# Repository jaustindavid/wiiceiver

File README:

http://austindavid.com/t/wiiceiver-github

The Wiiceiver is a drop-in "plug and play" replacement for a
standard R/C receiver.  It has a Nintendo Wii Nunchuck 
connection, a 3-pin ESC connector, and an available connector
for an external BEC if required.  

The Wiiceiver is intended for use on an electric skateboard.
The Y-axis (up/down) is throttle -- push up to speed up,
middle is neutral, down is brakes.  These function roughly
the same as on a standard RC transmitter.

Wiiceiver also implements a few additional functions:
- X/Y joystick axes, X/Y/Z accelerometers, and the two buttons 
  are monitored to confirm that the nunchuck is "active" -- 
  as opposed to dropped or low battery.  When "inactive" the
  wiiceiver returns to neutral, and will not re-start until 
  it detects and active neutral signal
- C button is "cruise control" -- press and hold C to maintain
  the current throttle level.  Drop the joystick to neutral to
  cruise.  While holding C, pressing the joystick "up" will
  increase speed gently, "down" will decrease speed.  
  Releasing C returns to neutral.
- Control smoothing: Wiiceiver implemenets an exponential 
  algorithm to smooth the controller input.  As currently
  tuned, an instant 0-100% throttle input will result in a
  gradual change to the ESC over the course of about 1s.
- 2.0 uses a "floating ceiling" for predictable acceleration
  damping and more responsive throttle.

It has been tested to work with a corded Nintendo nunchuck, a 
Memorex wireless nunchuck, and a Nyko Kama wireless nunchuck.

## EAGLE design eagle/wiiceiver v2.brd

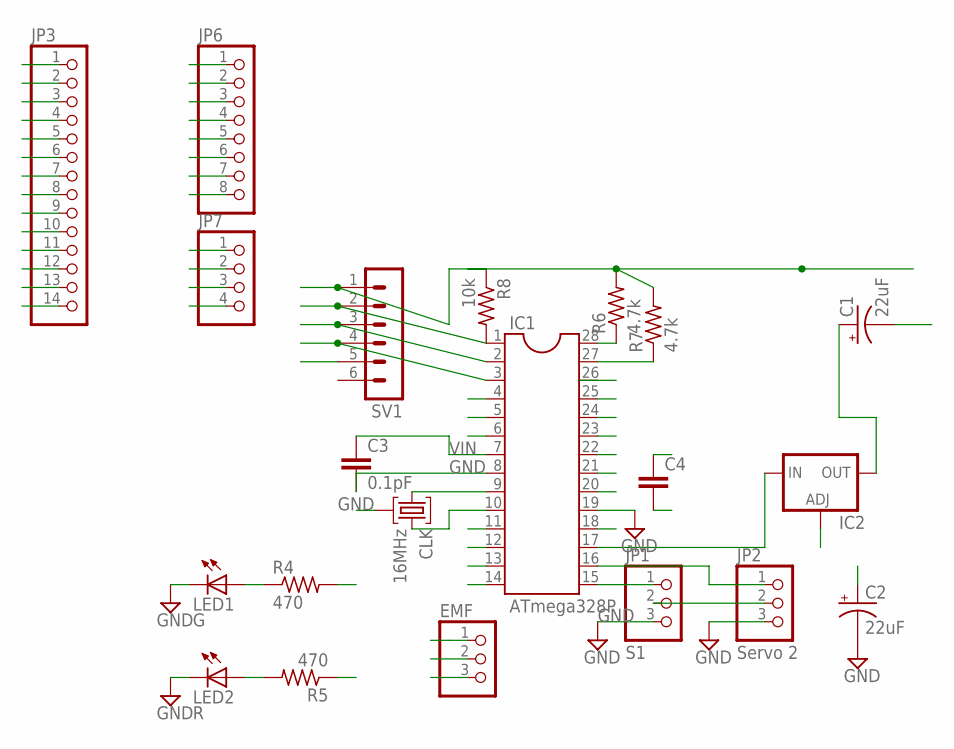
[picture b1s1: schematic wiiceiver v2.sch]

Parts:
C1, C2: 22uF; B45181A
C3: 0.1pF; C5B2.5
C4: C5/2.5; C5B2.5
CLK: 16MHz; HC49U
EMF: PINHD-1X3; 1X03
IC1: ATmega328P; DIL28-3
IC2: LM317TS; 317TS
JP1: S1; 1X03
JP2: Servo 2; 1X03
JP3: PINHD-1X14; 1X14
JP6: PINHD-1X8; 1X08
JP7: PINHD-1X4; 1X04
LED1: G; LED3MM
LED2: R; LED3MM
R4, R5: 470; 0204V
R6, R7: 4.7k; 0204V
R8: 10k; 0204V
SV1: MA06-1

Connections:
A0: IC1.23, JP3.6
A1: IC1.24, JP3.5
A2: IC1.25, JP3.4
A3: IC1.26, JP3.3
A4: IC1.27, JP3.2, R7.1
A5: IC1.28, JP3.1, R6.1
D0: IC1.2, JP6.2, SV1.3
D1: IC1.3, JP6.3, SV1.4
D2: IC1.4, JP6.4
D3: IC1.5, JP6.5
D4: IC1.6, JP6.6
D5: IC1.11, JP7.1
D6: IC1.12, JP7.2, R4.2
D7: IC1.13, JP7.3
D8: IC1.14, JP7.4, R5.1
D9: IC1.15, JP1.1, JP3.14
D10: IC1.16, JP2.1, JP3.13
D11: IC1.17, IC2.3 (IN), JP3.12
D12: IC1.18, JP3.11
D13: JP3.10
GND: C1.-, C2.-, C3.2, C4.2, CLK.2, EMF.2, IC1.8, IC1.19, IC1.22, IC2.1 (ADJ), JP1.3, JP2.3, JP3.7, JP6.8, LED1.K (C), LED2.K (C), SV1.5
unnamed: LED2.A, R5.2
unnamed: LED1.A, R4.1
unnamed: CLK.3, IC1.10
unnamed: CLK.1, IC1.9
unnamed: C1.+, IC2.2 (OUT)
RST: IC1.1, JP6.1, R8.2, SV1.2
VIN: C3.1, C4.1, EMF.3, IC1.7, IC1.20, IC1.21, JP3.8, JP3.9, JP6.7, R6.2, R7.2, R8.1, SV1.1
VRAW: C2.+, EMF.1, JP1.2, JP2.2

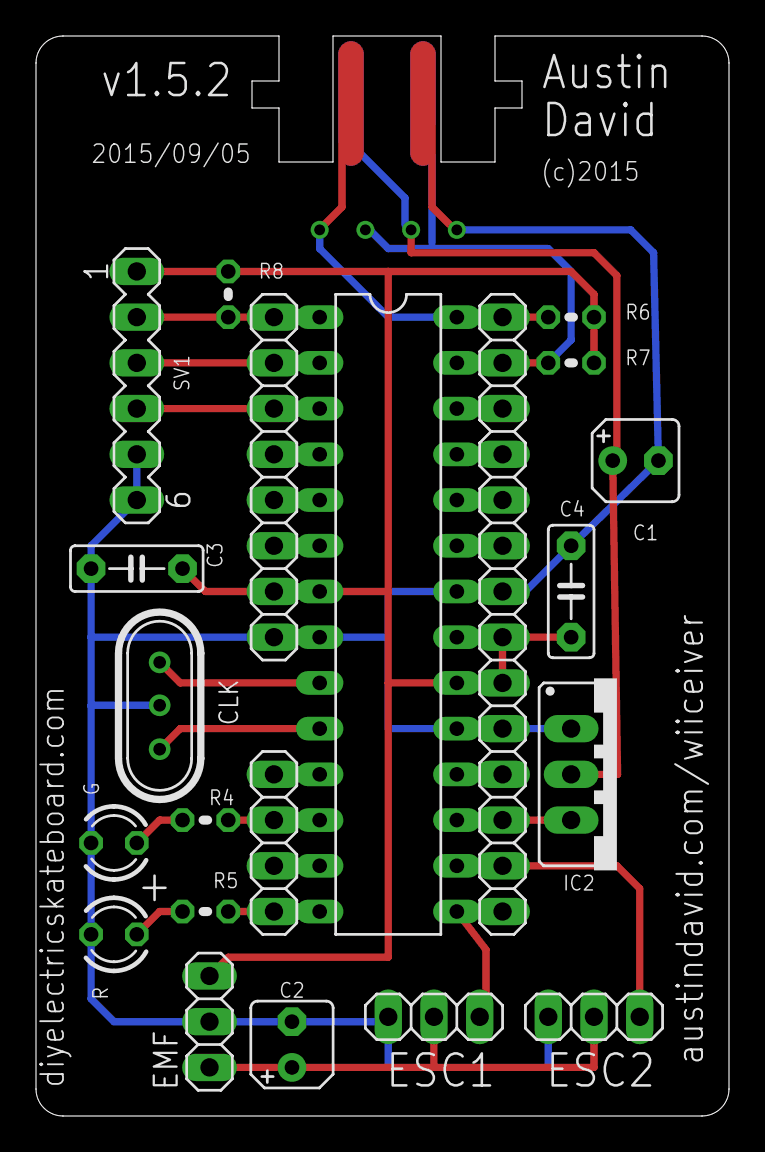
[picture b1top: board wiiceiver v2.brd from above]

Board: 2 copper layers, 38.5 x 60.0 mm, 21 parts (0 on the bottom side), 28 nets.

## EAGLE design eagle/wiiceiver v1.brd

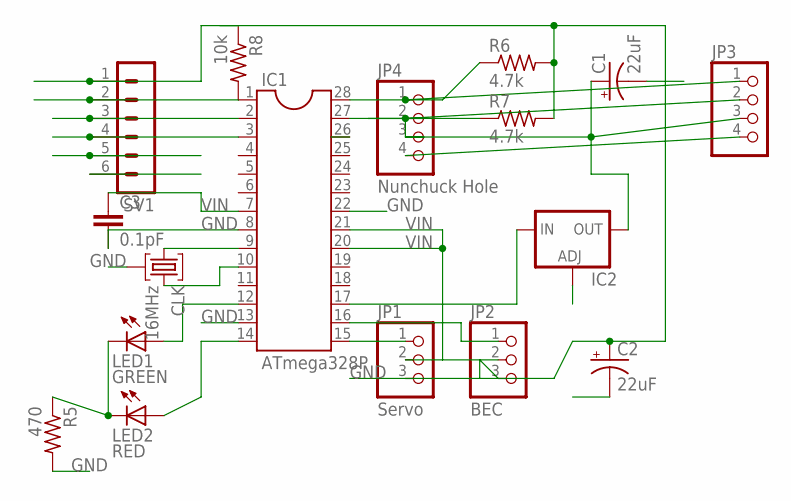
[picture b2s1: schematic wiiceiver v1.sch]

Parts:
C1, C2: 22uF; B45181A
C3: 0.1pF; C5B2.5
CLK: 16MHz; HC49U
IC1: ATmega328P; DIL28-3
IC2: LM317TS; 317TS
JP1: Servo; 1X03
JP2: BEC; 1X03
JP3: PINHD-1X4; 1X04
JP4: Nunchuck Hole; 1X04
LED1: GREEN; LED3MM
LED2: RED; LED3MM
R5: 470; 0204V
R6, R7: 4.7k; 0204V
R8: 10k; 0204V
SV1: MA06-1

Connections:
DIP12: IC1.12, LED1.A
GND: C1.-, C2.+, C2.-, C3.2, CLK.2, IC1.8, IC1.13, IC1.22, IC2.1 (ADJ), JP1.3, JP2.3, JP3.4, JP4.4, R5.2, R6.2, R7.2, R8.1, SV1.1, SV1.5, SV1.6
unnamed: IC1.15, JP1.1
unnamed: IC1.1, R8.2, SV1.2
unnamed: IC1.16, JP2.1
unnamed: LED1.K (C), LED2.K (C), R5.1
unnamed: IC1.14, LED2.A
unnamed: CLK.3, IC1.10
unnamed: IC1.17, IC2.3 (IN)
unnamed: CLK.1, IC1.9
unnamed: C1.+, IC2.2 (OUT), JP3.2, JP3.3, JP4.3
unnamed: IC1.28, JP3.1, JP4.1, R6.1
unnamed: IC1.27, JP4.2, R7.1
RX: IC1.2, SV1.3
TX: IC1.3, SV1.4
VIN: C3.1, IC1.7, IC1.20, IC1.21, JP1.2, JP2.2

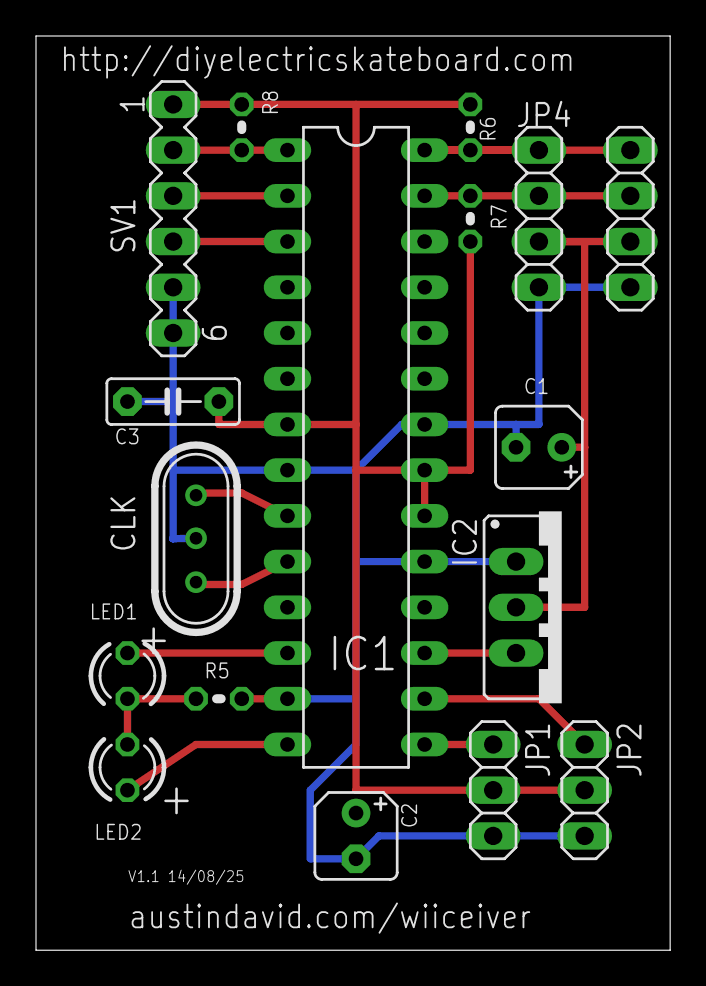
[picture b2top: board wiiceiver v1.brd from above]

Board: 2 copper layers, 35.2 x 50.8 mm, 17 parts (0 on the bottom side), 16 nets.

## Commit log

2014-05-09 new README
    pretty much what it sounds like
2014-05-09 archives: alternate parts
    implementations of an ATtiny84- and ATtiny85-based wiiceiver. These
    were the first two produced units, but were abandoned due to
    development and debugging problems.
2014-05-09 Working ATmega328-based Wiiceiver code
    “production” code for the ATmega328-based hardware
2014-05-10 fixing issue with over-updating ESC
    inadvertently in
2014-05-10 ignoring the local tool
    just a tool to copy from the Arduino working environment into the git
    repo
2014-05-10 re-adding calibration on startup
    re-added the older calibrate-on-startup code
    also cleaned up some debugging statements in Chuck.h leftover from a
    previous refactor
2014-05-10 refactoring throttle
    … adds buttery smoothness
2014-05-11 v1 layout change; initial cruise
    v1 board has a slightly different layout; adding a runtime
    board-detection algorithm & pin mapping.
    Also adds minimum / initial cruise control — holding C at startup or
    very low speeds will accelerate to the specified minimum (currently
    0.10 == 10%)
2014-05-12 autoCruise !!
    a default 10%, configurable “autoCruise” level.
2014-05-13 RC1
    updates the activity detection, all 6 bytes.
2014-05-13 RC2
    added CC BY-NC-SA 4.0 attribution, comments / disclaimers, and some
    minor code cleanup.
2014-05-16 eagle schematics
    Schematics / layout of the wiiceiver v1 hardware
2014-05-17 re-grab cruise; better brakes -> throttle
    re-grab cruise: if you drop cruise and idle (no stick input) for fewer
    than 5 seconds, hitting C will return the previous cruise speed. Time
    is configurable with THROTTLE_CRUISE_RETURN_MS
    brakes->throttle: previously the return from braking to neutral was
    “smoothed” — hitting brakes & letting go is a gradual let-go. That’s
    fixed now, it lets go of brakes immediately.
2014-05-17 recording the time we last changed the ESC
2014-05-19 don't smooth brakes
    braking (and releasing) is now unsmoothed, totally responsive.
2014-05-20 better brake-smoothing
2014-05-22 ordered!
    “final” version, ordered from OshPark
2014-05-24 A fix to live-restart the Kama
    Nyko Kama is sorta weird about getting restarted. This might fix it.
    The memorex + hardwired chuck both still work also.
2014-05-24 more gently restarting the Kama
    Kama will crash the I2C bus on hard restart, so we don’t do that
    anymore. A few live re-inits seem to be enough (while bench-testing)
2014-05-24 exposing smoothing limits for 1s / 2s options
    see above
2014-05-25 fine-tuning the Servo
    now forcing Servo to 1000/2000ms, adding debug output to confirm the
    actual pulse width, putting the angles out to 0/180, and tinkering with
    the ESC initialization sequence.
    ESC still doesn’t initialize quickly, but everything else tests fine.
2014-05-25 fixing ESC sync?
2014-05-26 "Beta" release candidate
    Includes fixes for all known issues
    * Fast (perfect?) ESC sync
    * fast / continuous Kama restart
    * ESCs exactly 1000-2000us, midpoint exactly 1500us
2014-05-28 ESC sync up again
2014-05-28 still tinkering with ESC sync
2014-05-29 More attempted ESC mucking
    changes the ESC init code, and some mods to Z-button handling. Z==no
    smoothing under throttle
2014-06-03 updating PCB slightly
    6-pin header was a little tight…
2014-06-05 wow, a bug!
    found a legit bug. Nutty!
2014-06-10 resets wiiciever to "factory" default
    Running / loading this sketch will overwrite stored values for
    auto-cruise and nunchuck calibration, as if the chip were brand new.
    This is NOT a functioning wiiceiver!
    On success, both red and green lights will be lit. If one or both are
    not lit, something bad happened
2014-06-10 docs
2014-07-24 adaptive smoothing via floating ceiling
    uses a floating ceiling in smoother, for an adaptive smoothing. Also
    uses a program map: 5 programs (brakes, throttle, throttle + z, cruise,
    cruise + z) with 3 tunables in each (ceiling up, ceiling down,
    smoothness).
    Still needs some cleanup and a shitload of testing before RC-worthy
2014-07-25 cleanup pass
    deleted some code, some minor refactoring and cleaning up. More to
    come, but first road test is promising
2014-07-25 beta-quality?
    smoothness & cruise are unsurprising. Throttle feels good.
2014-07-26 some cleanup around autoCruise
    cleaning code around autoCruise, to make it harder to set accidentally.
2014-07-27 autoCruise is harder to set
    autoCruise now requires Z + more precise X deflection, and only takes a
    setting within 2 minutes of startup.
2014-08-01 added a watchdog
    using the watchdog timer @ 250ms to (hopefully) catch a hardware glitch.
2014-08-01 cleanup time
2014-08-01 cleanup; Z == raw stick
    some more code cleanup, and updated Z throttle program to be 100% (no
    smoothing)
2014-08-01 minor cleanup
2014-08-03 watchdog cleanup
    more watchdog work; now an 8S timer in freakout / inactive mode, as
    there are many built-in delays while resyncing
2014-08-05 working on cruise resume
    adding some unfortunate complexity in CCR (check cruise return), to
    track intermediate states. This allows us to resume from cruise in a
    similar manner to acceleration, including a new “resume” smoothing
    program.
2014-08-08 adding an "Experimental" sketch
    not a branch, because Arduino :/
2014-08-08 cleanup for 1.1 release candidate
    minor cleanup
2014-08-08 code cleanup
2014-08-09 stores & recalls history
    uses EEPROMAnything; probably should switch to EEPROMex…
2014-08-09 updating docs
2014-08-09 templating StaticQueue
2014-08-09 test candidate!
2014-08-11 minor cleanup, including history
    no longer prints empty records in the history
2014-08-11 fixing a hilarious bug in auto-cruise
    the bug: dropping cruise DURING A (SLOW) RESUME would save the
    possibly-quite-slow “previous cruise speed”, possibly lower than the
    auto-cruise level. This is not intentional, as auto cruise should be
    the slowest possible cruise speed.
    also fattened the “cancel cruise” input range to 10%, I think touchy
    nunchucks are accidentally killing resume function :/
2014-08-11 pulling in Wiiceiver_X to an "experimental" branch
    Looks for an analog signal on A1; see Logger.h for details.
2014-08-11 dropping Wiiceiver_X
    /me rolls eyes @ Arduino IDE
2014-08-11 bumping rev to proper 1.2-exp
2014-08-11 text!
2014-08-12 more slack to kill cruise
    increasing the amount of input required to cancel CC
2014-08-17 Display! Adafruit 128x32
    adds an i2c display, still WIP
2014-08-17 cleanup around status messaging
    Hitting Z returns to the previous screen (correctly).
    adds a “History” screen showing the previous few rides’ consumption
2014-08-17 prettying the display
2014-08-20 Moving display code to _head
    Wiiceiver_master is a display-aware Wiiceiver base. Sadly, it’s up
    against memory limits. It sends a buffer (struct) out the i2c hole.
    Wiiceiver_head is a totally different codebase, designed to drive / act
    as a frame buffer for an Adafruit display based on SSD1306.
    Wiiceiver_head is intended to run on a separate Arduino (possibly pro
    mini), SPI-attached to the display.
2014-08-20 spit & polish
2014-08-21 bugfixes & tested
    works frealz
2014-08-23 formerly known as Wiiceiver_head
2014-08-23 has been renamed Wiiceiver_Display
2014-08-24 some cleanup & tweaking
    history now shows previous 3 rides (formerly: 0 == current, 1/2 =
    previous 2). Some code cleanup. “Current (A)” now shows moving
    average of previous 10, which is roughly 1/2 second, to smooth out the
    display.
2014-08-26 slight mod to v1
    adding an extra ESC port, i2c pads, and a logo
2014-08-29 alpha-quality?
    adds a sort of timeout for the master, a fuel gauge in the Discharge
    screen, few more vars, fixes a naive implementation (bug) in StaticQueue
    still some gaps in the startup sequence
2014-08-29 fixes issue #5
    uptime fix on the “status” (throttle) screen
2014-08-29 default to *not* FAKE_AMMETER
    leave the debugging ammeter OFF in committed code :/
2014-09-04 v 1.6 exp: partial voltage implementation
    new Voltage screen, removed Watchdog, many display updates and memory
    optimization. Debugging is hard when you have no idea why it crashes :/
2014-09-05 some cleanup, and added Watts
    a self-computed Watts screen in the display. Also fixes some minor
    bugs in a few screens, and an OBO error in StaticQueue
2014-09-05 REAL sensors
    … not fake ones.
2014-09-06 persistent / smart fuel gauge
    Wiiceiver_master retains “accumulated discharge” state, and resets if
    the voltage is higher than some level — detecting if the board was
    recharged. The fuel level shown in Wiiceiver_display uses this
    accumulated discharge / reset, to always show what it thinks is the
    remaining charge in the pack.
2014-09-11 incorporating phomann's V2 layout
    adding dual ESC support into the 1.x line and layout changes for Peter
    Homann’s awesome V2 SMD-based board.
    Backward compatible with v0 / v1 boards.
2014-09-11 doc update
    adding http://www.homanndesigns.com URL for the V2 layout
2014-09-13 1.2.1 -- dual ESC for v1 / v2 boards
    early V1 boards only have omen ESC port, but newer ones (which don’t
    otherwise self-identify) have it. Enable it for all of them, just in
    case.
2014-10-17 minor update for calibration function
    calibrates in 1s now, and more reliably
    also some minor changes to the schematic, fixing glitches
2014-10-20 updated layouts
    new PCBS!
2014-10-20 cleaning up
2015-09-24 new "1.3" code; significant smoother & cruise changes
2015-09-28 2.0 codebase, first drop
    includes full setup routine, cruise+drag brake control, new ESC sync
    routine, etc. A few minor nits, but down to fine-tuning at this point.
2015-09-28 consolidating sketches: there can be only one (2.0)
    The 2.0 drop, in its own branch
2015-09-28 a 1.5.2 customization for one guy
    “followtheblacksheep.com”
2015-09-28 catching up, 1.5.x layouts
2015-09-28 no longer required
    2.0 includes a factory reset function built-in
2015-09-30 cleanup & fix for IDE 1.6.x
    some internal cleanup, mostly nonfunctional changes
2015-10-02 s/tuna/Tuna/
2015-10-12 beta3: minor fix in the setup routine
    the throttle setup didn’t start the ESC until the setting was changed;
    that’s silly.
2015-10-12 added a "Heli" mode; code cleanup
    Significant cleanup for the debugging functions, removes a LOT of RAM
    pressure.
    Adds a compiled-out “heli” mode for heli/airplane ESCs. More work
    needed, but it makes them usable now.
2015-10-15 moving *2.0 code to the 2.0 branch
    removing 1.3 and 2.0 from ‘master’ branch; it’s in 2.0
2016-02-23 prototypes
    Chuck is a handheld unit; Wiiceiver_Base (working title) is the
    corresponding receiver & servo driver.
2016-03-16 adds Wiiceiver Surf {Base, Chuck}; bug fix in Wiiceiver -> 2.0b4
    new hardware incoming, the surf chuck & board. Details to follow.
    In “classic” wiiceiver code there was a bug in the coasting code, now
    resolved. Also adds a feature to set a max throttle limit, and
    correctly scales that to the positive Y axis
2016-03-16 some final 2.0b4 cleanup
    fixing debugging statements, removing hell mode by default
2016-05-14 catching up; Board + Chuck (sorta) work
    significant catchup. Chuck has a compile-time way to act like a
    nunchuck or a “fake” chuck. Lots of work needed for cleanup, but it’s
    there.
    Board has a way to FORCE heli-mode … not very pretty, there’s not a
    good way to un-force. Need to work on this more. otherwise, also
    works. Enabled for quad ESC now, need to test.

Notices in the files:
eagle/wiiceiver v2.brd:
(c)2015
